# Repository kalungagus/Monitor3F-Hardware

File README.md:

# Monitor3F-Hardware
O projeto atual está destinado ao monitoramento de potência trifásica de uma máquina. Ele foi desenvolvido para levantar as curvas de potência de tornos e fresadoras. Para isto, emprega-se divisores de tensão que estarão ligados a cada fase da máquina através de transformadores. Depois há um divisor de tensão para reduzir a tensão para níveis aceitos por um ESP32 e finalmente adiciona-se uma componente DC de 3.5V e isola-se esta tensão resultante do ESP32 através de um buffer.
O mesmo acontece com o monitoramento de corrente, que é feito através de um transformador de corrente ligado a um resistor. O sinal de corrente também é adicionado a uma componente DC de 3.5V e isolado do ESP32 por um buffer.

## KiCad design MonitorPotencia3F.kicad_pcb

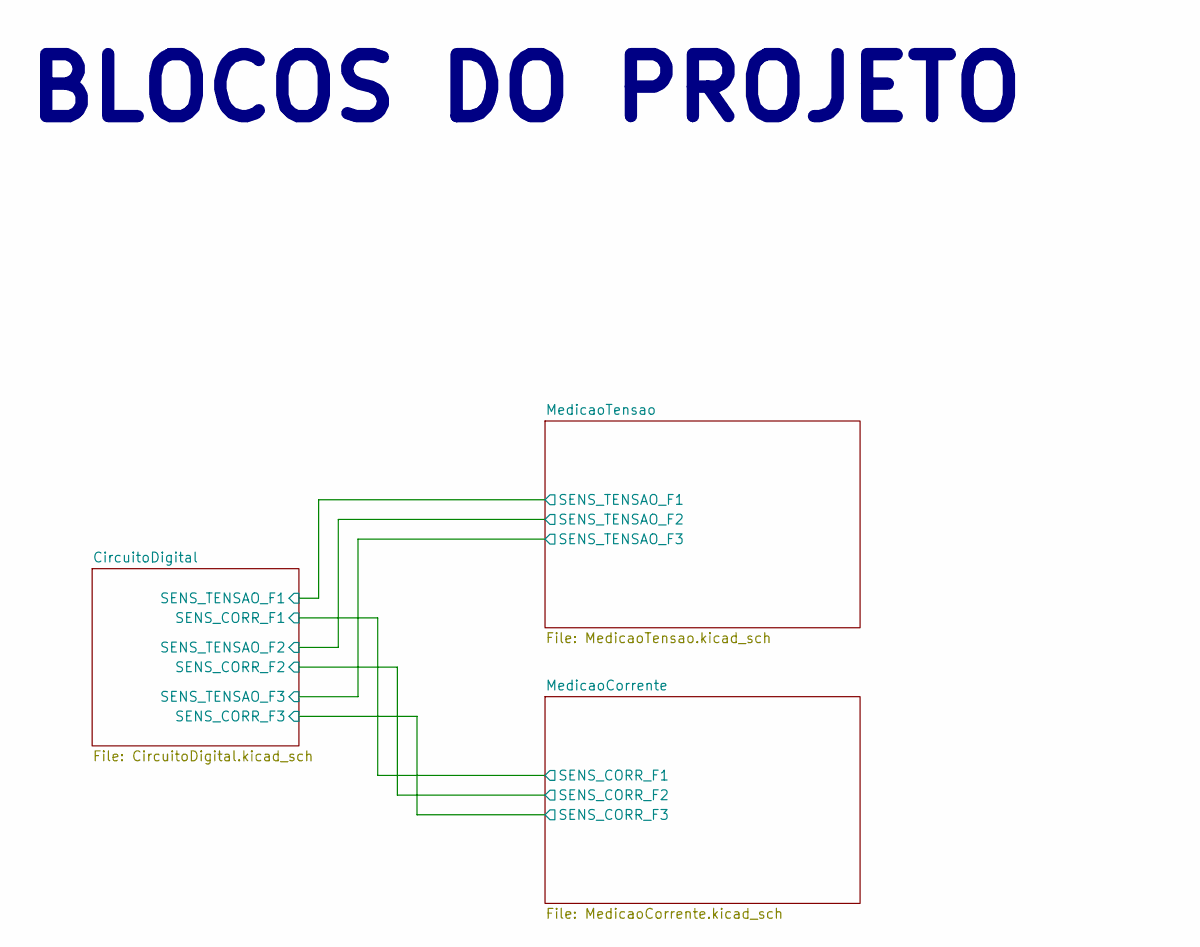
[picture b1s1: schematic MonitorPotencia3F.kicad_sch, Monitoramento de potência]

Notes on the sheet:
BLOCOS DO PROJETO

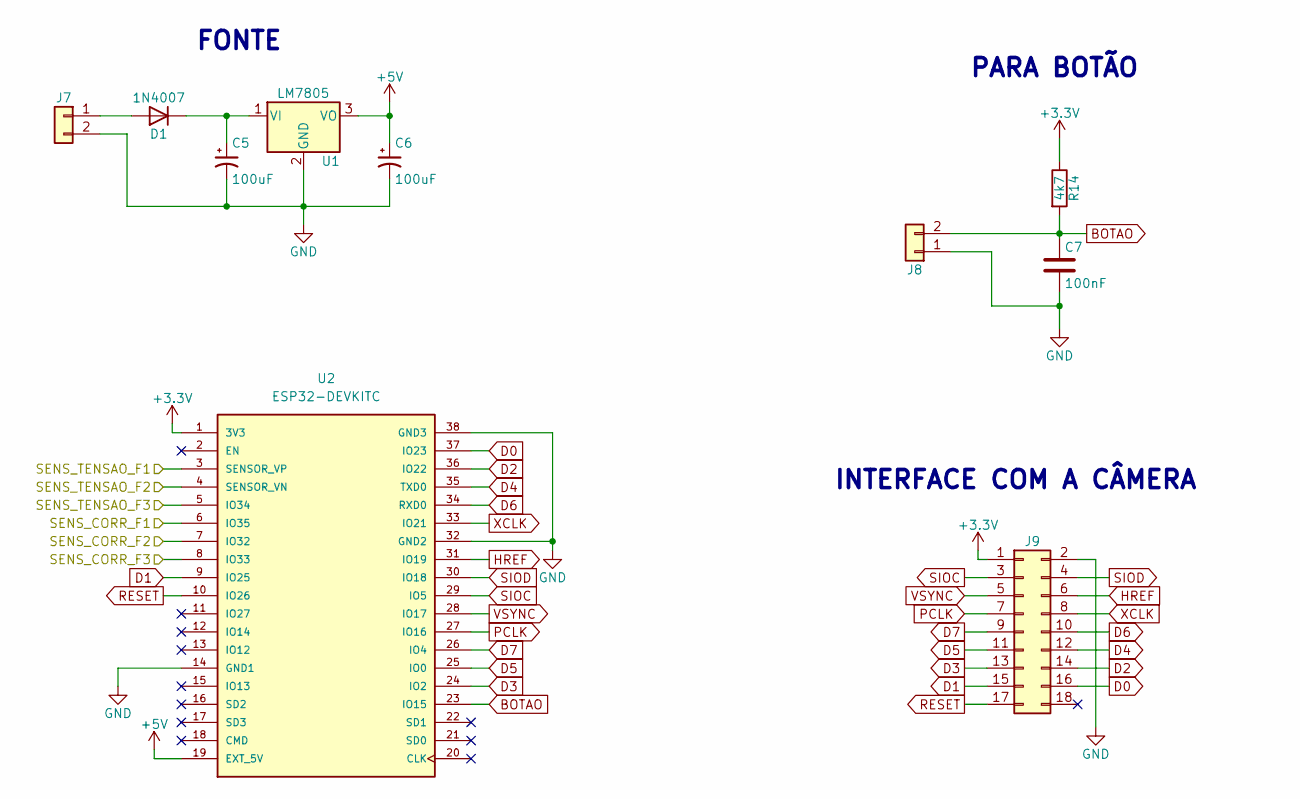
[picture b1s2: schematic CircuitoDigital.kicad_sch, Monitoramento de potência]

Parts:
C5, C6: 100uF; CP_Radial_D6.3mm_P2.50mm
C7: 100nF; C_Rect_L7.0mm_W2.0mm_P5.00mm
D1: 1N4007; D_DO-41_SOD81_P10.16mm_Horizontal
J7, J8: Conn_01x02; TerminalBlock_bornier-2_P5.08mm
J9: Conn_02x09_Odd_Even; PinHeader_2x09_P2.54mm_Vertical
R14: 4k7; R_Axial_DIN0207_L6.3mm_D2.5mm_P10.16mm_Horizontal
U1: LM7805; TO-220-3_Vertical
U2: ESP32-DEVKITC; MODULE_ESP32-DEVKITC; PARTREV N/A

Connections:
+3V3: J9.1, R14.1, U2.1 (3V3); also elsewhere on the board
+5V: C6.1, U1.3 (VO), U2.19 (EXT_5V); also elsewhere on the board
/CircuitoDigital/SENS_CORR_F1: U2.6 (IO35); also elsewhere on the board
/CircuitoDigital/SENS_CORR_F2: U2.7 (IO32); also elsewhere on the board
/CircuitoDigital/SENS_CORR_F3: U2.8 (IO33); also elsewhere on the board
/CircuitoDigital/SENS_TENSAO_F1: U2.3 (SENSOR_VP); also elsewhere on the board
/CircuitoDigital/SENS_TENSAO_F2: U2.4 (SENSOR_VN); also elsewhere on the board
/CircuitoDigital/SENS_TENSAO_F3: U2.5 (IO34); also elsewhere on the board
BOTAO: C7.1, J8.2, R14.2, U2.23 (IO15)
D0: J9.16, U2.37 (IO23)
D1: J9.15, U2.9 (IO25)
D2: J9.14, U2.36 (IO22)
D3: J9.13, U2.24 (IO2)
D4: J9.12, U2.35 (TXD0)
D5: J9.11, U2.25 (IO0)
D6: J9.10, U2.34 (RXD0)
D7: J9.9, U2.26 (IO4)
GND: C5.2, C6.2, C7.2, J7.2, J8.1, J9.2, U1.2 (GND), U2.14 (GND1), U2.32 (GND2), U2.38 (GND3); also elsewhere on the board
HREF: J9.6, U2.31 (IO19)
unnamed: C5.1, D1.1 (K), U1.1 (VI)
unnamed: D1.2 (A), J7.1
PCLK: J9.7, U2.27 (IO16)
RESET: J9.17, U2.10 (IO26)
SIOC: J9.3, U2.29 (IO5)
SIOD: J9.4, U2.30 (IO18)
VSYNC: J9.5, U2.28 (IO17)
XCLK: J9.8, U2.33 (IO21)

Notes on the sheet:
INTERFACE COM A CÂMERA
PARA BOTÃO
FONTE

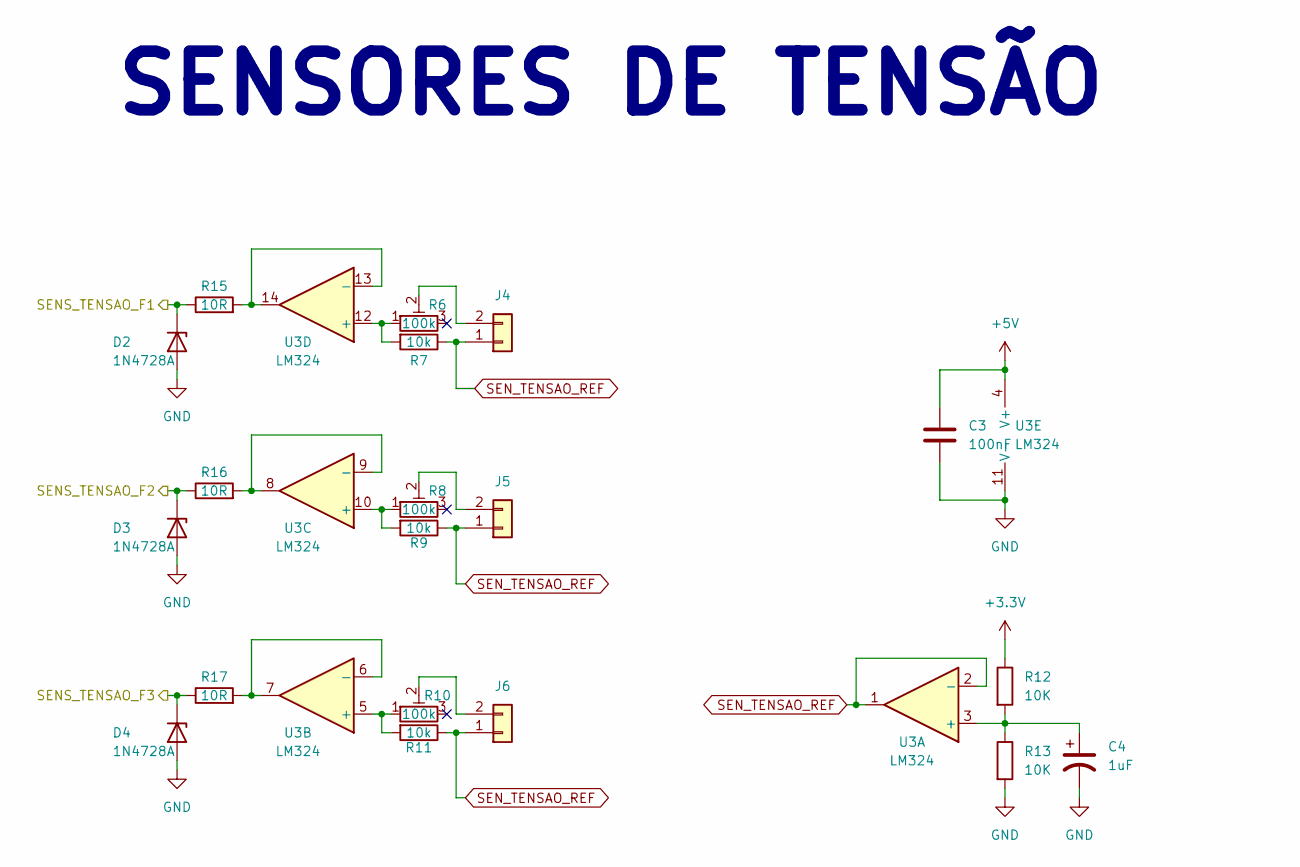
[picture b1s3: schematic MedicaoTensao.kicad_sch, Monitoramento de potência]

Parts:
C3: 100nF; C_Rect_L7.0mm_W2.0mm_P5.00mm
C4: 1uF; CP_Radial_D6.3mm_P2.50mm
D2, D3, D4: 1N4728A; D_DO-41_SOD81_P10.16mm_Horizontal
J4, J5, J6: Conn_01x02; TerminalBlock_bornier-2_P5.08mm
R6, R8, R10: 100k; Potentiometer_Bourns_3296W_Vertical
R7, R9, R11: 10k; R_Axial_DIN0207_L6.3mm_D2.5mm_P10.16mm_Horizontal
R12, R13: 10K; R_Axial_DIN0207_L6.3mm_D2.5mm_P2.54mm_Vertical
R15, R16, R17: 10R; R_Axial_DIN0207_L6.3mm_D2.5mm_P2.54mm_Vertical
U3: LM324; DIP-14_W7.62mm

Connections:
+3V3: R12.1; also elsewhere on the board
+5V: C3.1, U3.4 (V+); also elsewhere on the board
/CircuitoDigital/SENS_TENSAO_F1: D2.1 (K), R15.1; also elsewhere on the board
/CircuitoDigital/SENS_TENSAO_F2: D3.1 (K), R16.1; also elsewhere on the board
/CircuitoDigital/SENS_TENSAO_F3: D4.1 (K), R17.1; also elsewhere on the board
GND: C3.2, C4.2, D2.2 (A), D3.2 (A), D4.2 (A), R13.2, U3.11 (V-); also elsewhere on the board
unnamed: C4.1, R12.2, R13.1, U3.3 (+)
unnamed: J4.2, R6.2
unnamed: J5.2, R8.2
unnamed: J6.2, R10.2
unnamed: R6.1, R7.2, U3.12 (+)
unnamed: R8.1, R9.2, U3.10 (+)
unnamed: R10.1, R11.2, U3.5 (+)
unnamed: R15.2, U3.13 (-), U3.14
unnamed: R16.2, U3.8, U3.9 (-)
unnamed: R17.2, U3.6 (-), U3.7
SEN_TENSAO_REF: J4.1, J5.1, J6.1, R7.1, R9.1, R11.1, U3.1, U3.2 (-)

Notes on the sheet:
SENSORES DE TENSÃO

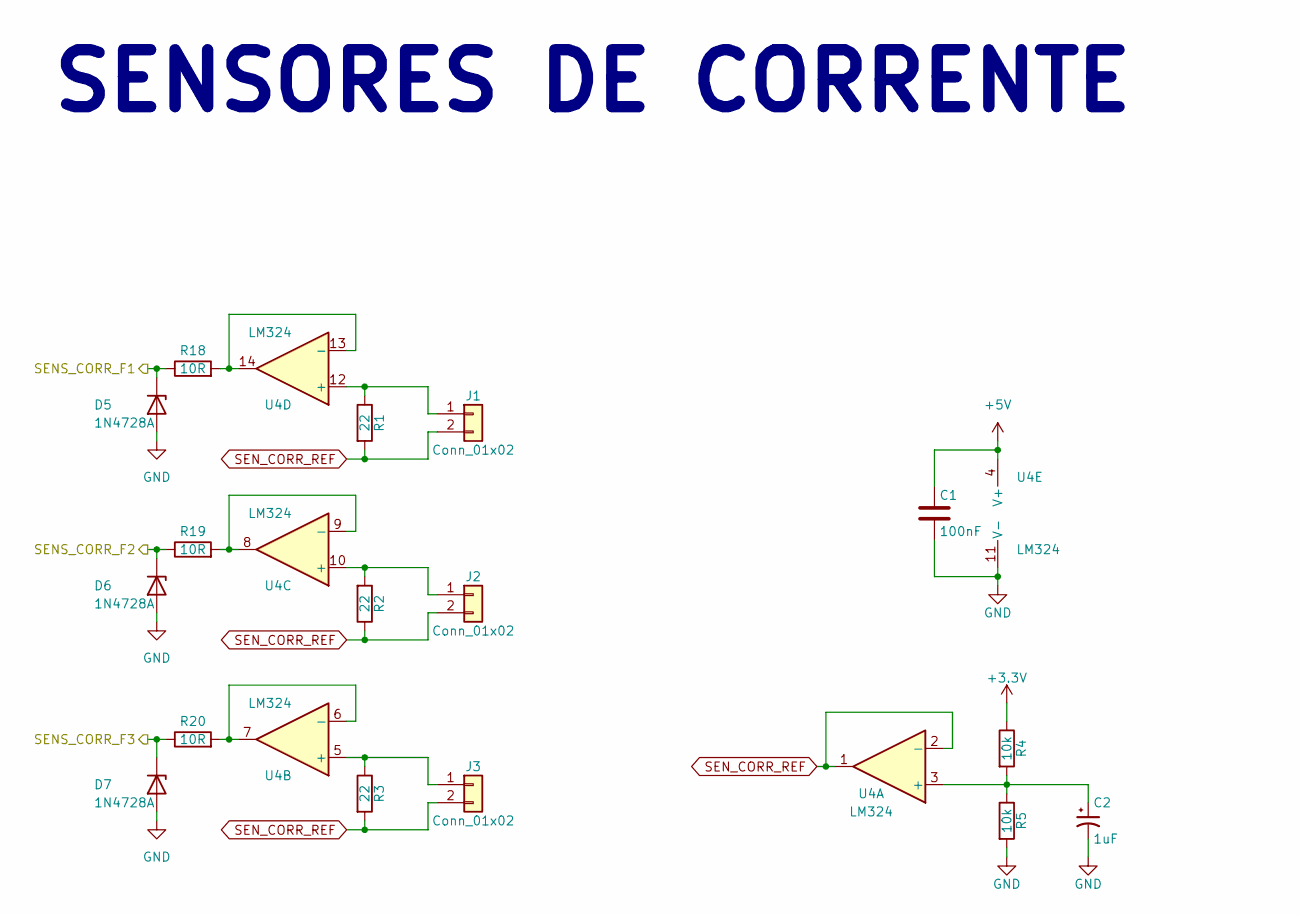
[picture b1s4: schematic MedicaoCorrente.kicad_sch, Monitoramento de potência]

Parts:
C1: 100nF; C_Rect_L7.0mm_W2.0mm_P5.00mm
C2: 1uF; CP_Radial_D6.3mm_P2.50mm
D5, D6, D7: 1N4728A; D_DO-41_SOD81_P10.16mm_Horizontal
J1, J2, J3: Conn_01x02; TerminalBlock_bornier-2_P5.08mm
R1, R2, R3: 22; R_Axial_DIN0207_L6.3mm_D2.5mm_P10.16mm_Horizontal
R4, R5: 10k; R_Axial_DIN0207_L6.3mm_D2.5mm_P10.16mm_Horizontal
R18, R19, R20: 10R; R_Axial_DIN0207_L6.3mm_D2.5mm_P2.54mm_Vertical
U4: LM324; DIP-14_W7.62mm

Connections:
+3V3: R4.1; also elsewhere on the board
+5V: C1.1, U4.4 (V+); also elsewhere on the board
/CircuitoDigital/SENS_CORR_F1: D5.1 (K), R18.1; also elsewhere on the board
/CircuitoDigital/SENS_CORR_F2: D6.1 (K), R19.1; also elsewhere on the board
/CircuitoDigital/SENS_CORR_F3: D7.1 (K), R20.1; also elsewhere on the board
GND: C1.2, C2.2, D5.2 (A), D6.2 (A), D7.2 (A), R5.2, U4.11 (V-); also elsewhere on the board
unnamed: C2.1, R4.2, R5.1, U4.3 (+)
unnamed: J1.1, R1.1, U4.12 (+)
unnamed: J2.1, R2.2, U4.10 (+)
unnamed: J3.1, R3.1, U4.5 (+)
unnamed: R18.2, U4.13 (-), U4.14
unnamed: R19.2, U4.8, U4.9 (-)
unnamed: R20.2, U4.6 (-), U4.7
SEN_CORR_REF: J1.2, J2.2, J3.2, R1.2, R2.1, R3.2, U4.1, U4.2 (-)

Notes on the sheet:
SENSORES DE CORRENTE

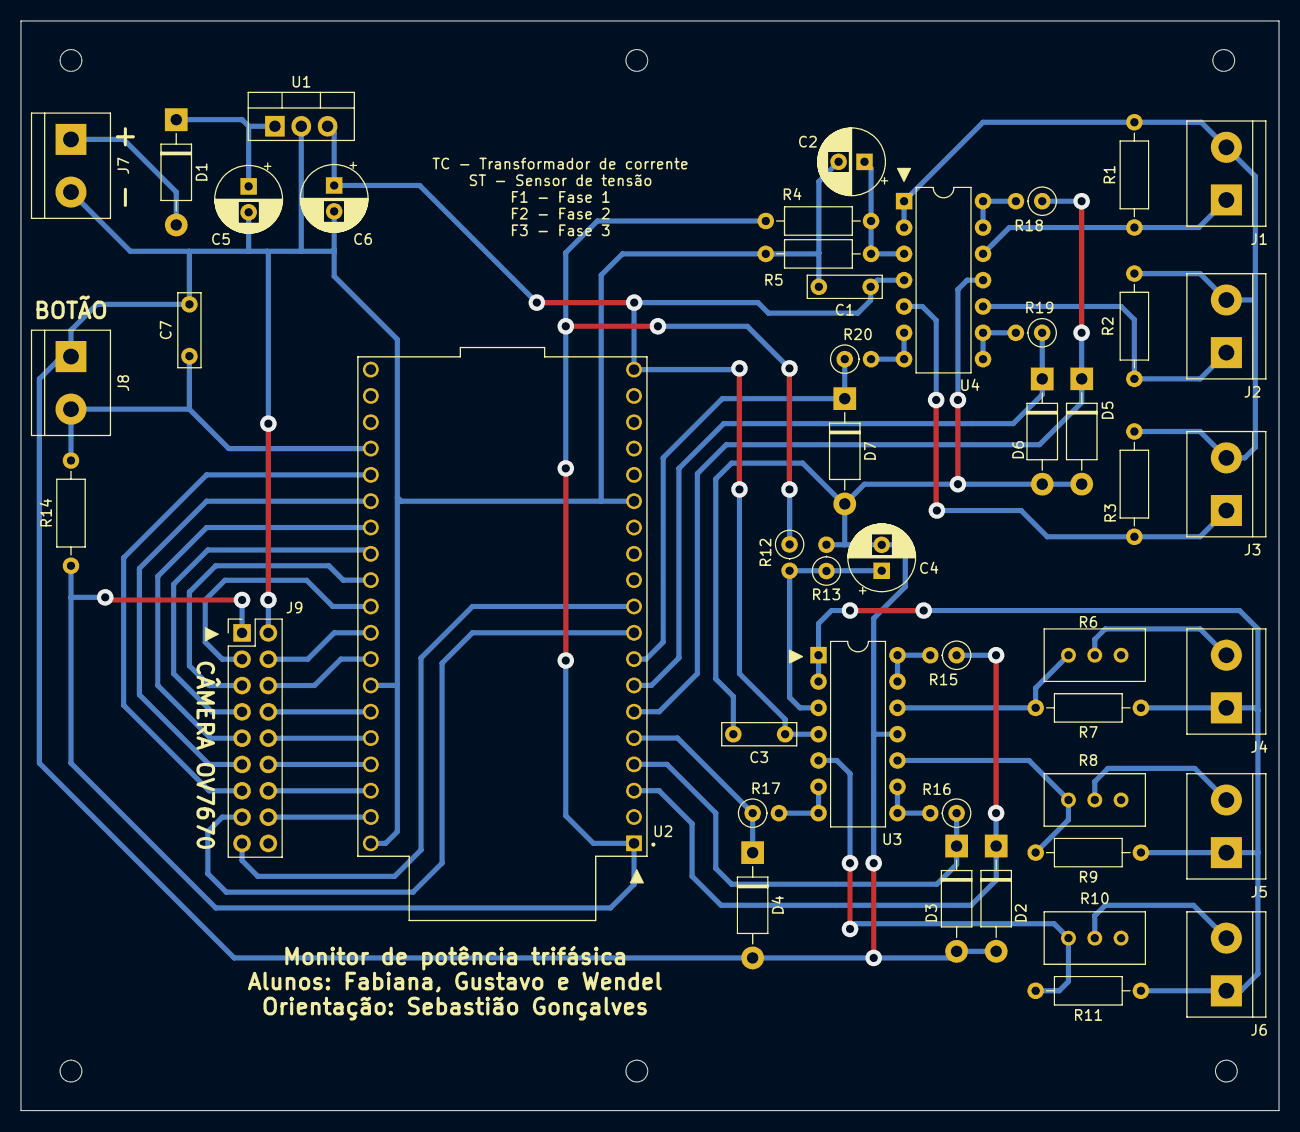
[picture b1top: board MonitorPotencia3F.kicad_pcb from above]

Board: 2 copper layers, 121.4 x 105.2 mm, 47 parts (0 on the bottom side), 46 nets.

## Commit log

2022-04-07 Commit inicial do projeto. Esta versão foi produzida para um sensor de tensão externo, com interface para câmera e circuito para sensor de corrente. Ainda existe um botão para iniciar a operação.
2022-04-07 Atualização do projeto com novos sensores de tensão. A referência de tensão para os sensores de corrente também foi atualizada, incluindo um buffer para isolação do divisor de tensão. Os Footprints t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
2022-04-08 Adicionado arquivo de Layout
2022-04-08 Adicionado trimpots para a regulagem da entrada dos sensores de tensão. Adicionou-se também um capacitor de desacolpamento para o ESP32.
2022-04-11 Adicionado zeners de proteção para a saída dos buffers
2022-04-16 As proteções nas saídas dos amplificadores operacionais foram melhoradas e os trimpots foram substituídos por trimpots de 3 pinos, para refletir os que são comprados por aqui.
2022-04-16 Definido todos os footprints para os componentes e feito o DRC
2022-04-19 PCB e modelo 3D foram completados. As alterações necessárias foram feitas no esquemático para refletir o projeto desenvolvido na PCB. Teve-se que alterar o modelo do ESP32 para aquele que foi adquiri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
